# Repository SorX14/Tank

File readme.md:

## Tank ##

A project to learn about I2C comms and create a tank capable of travelling over tough terrain operating in manual PC, manual RC or full auto waypointing mode.

The design is centred around separate modules offloading the processing for each part to a separate processor. Most of this is wasteful as the chips are capable of much more, but I wanted to learn about I2C.

The tank has 2 standard RC ESCs with reverse, so require servo signalling which Ardiuno supports easily.

The controller board uses the much more powerful Teensy 3.1 which does all of the heavy lifting, and also powers a small OLED screen showing the current status.

It can be controlled with a normal RC transmitter, or using a radio linked to a PC. GPS coordinates can also be loaded into the tank to allow autonomous operation.

### PCB ###
Each PCB has its own readme in the seperate directories. All PCBs were ordered through [OSHPark](https://oshpark.com/) and they took 1 week to arrive once they're made by the fab house.

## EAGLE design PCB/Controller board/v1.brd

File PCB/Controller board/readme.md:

## Controller board ##

Connecting using the same RJ45 connector, this board has the 'brains' and radio modules for the tank.

The brains are provided by a [Teensy 3.1](https://www.pjrc.com/teensy/teensy31.html) which is a powerful, compact microprocessor by PJRC. The footprint was provided by forum user **Constantin**, available [here](http://forum.pjrc.com/threads/24637-Updated-Teensy-3-1-and-Teensy-3-0-Eagle-libraries). The Teensy 3.1. has multiple SPI, I2C and serial connections which is really useful for debugging and interfacing with other modules. Most importantly, the Teensy 3.1 has an Arduino compatible IDE addon - [TeensyDuino](https://www.pjrc.com/teensy/teensyduino.html) - which makes writing code for it much more familiar.

The radio is provided by an [ARF](http://shop.ciseco.co.uk/arf-high-power-radio-transceiver/) from Ciseco using their Eagle footprints. It could just as easily by an XRF, or XBEE as they are pin compatible.

There is also a footprint for an [SSD1306 OLED 128x64 display](http://forum.hobbycomponents.com/viewtopic.php?f=39&t=1517) which **bernebeer** made. 

The board also has a CR2032 battery holder footprint on the back which connects to the Teensy VBAT connection which keeps the built in RTC running.

There is a 'GPS' header with selectable voltage output - either 3.3v or 5v. This header is just a connection to a serial port on the Teensy so could be used for other modules.

The reset pad underneath the Teensy was designed to be soldered to one of the rectangular pads on the bottom of the Teensy with a short wire. The Teensy can reset itself via software, so its possible to tri-state this pin; reading the status or sending a reset pulse to other modules.

There are a couple of test points around the board for various voltages, or serial comms. There are 4 PWM pins available between the Teensy and the display.

There are RC controller headers, which will accept the signals generated by a standard RC receiver.

There are 2 'servo' outputs which will be used to control a RC car ESC.

### Parts list ###

- **Passives** - Not going to list them, all 0805 sized
- **RJ45 connector** - Molex 85504-5001 - Farnell no: 2313732
- **CR2032 holder** - Keystone 3 002 - RS Stock No: 219-7954
- **Watch crystal** - FOX ELECTRONICS NC26LF-327 - Farnell no: 2064057 (needed for the Teensy 3.1 to keep the time)

### Mistakes ###

The GPS header has the wrong silkscreen on it, so the GND and VCC are reversed. Most GPS units can handle reverse voltage, but double-check.

### Resources ###

- **PCB top** [https://github.com/SorX14/Tank/blob/master/PCB/Controller%20board/top.png](https://github.com/SorX14/Tank/blob/master/PCB/Controller%20board/top.png)
- **PCB bottom** [https://github.com/SorX14/Tank/blob/master/PCB/Controller%20board/bottom.png](https://github.com/SorX14/Tank/blob/master/PCB/Controller%20board/bottom.png)

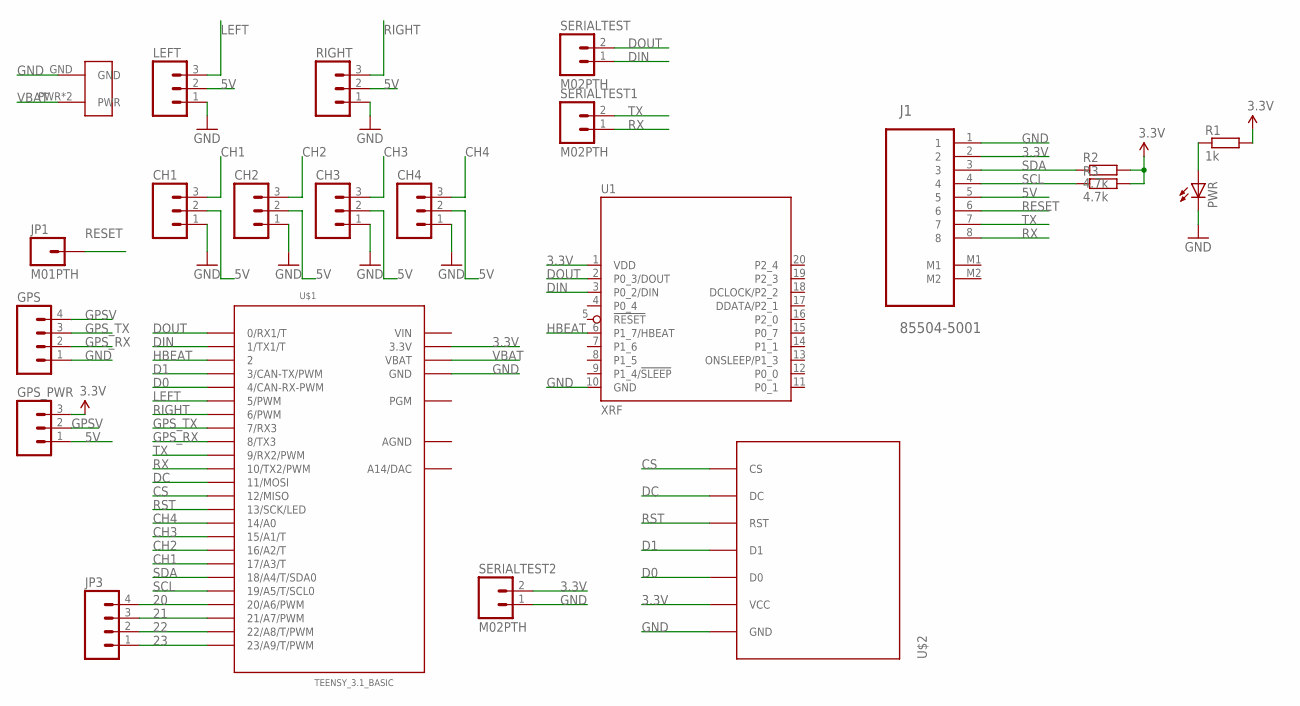
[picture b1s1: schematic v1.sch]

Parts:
CH1, CH2, CH3, CH4: M03PTH; 1X03
GPS: M04PTH; 1X04
GPS_PWR: M03PTH; 1X03
J1: 85504-5001; MOLEX_85504-5001
JP1: M01PTH; 1X01
JP3: M04PTH; 1X04
LEFT: M03PTH; 1X03
PWR: LEDCHIPLED_0805; CHIPLED_0805
R1: 1k; R0805
R2, R3: 4.7k; R0805
RIGHT: M03PTH; 1X03
SERIALTEST, SERIALTEST1, SERIALTEST2: M02PTH; 1X02
U1: XRF
U$1: TEENSY_3.1_BASIC
U$2: OLED_SSD1306_SPI
U$3: COINCELL

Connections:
3.3V: GPS_PWR.3, J1.2, R1.2, R2.2, R3.2, SERIALTEST2.2, U1.1 (VDD), U$1.3.3V, U$1.3.3V1 (3.3V), U$2.VCC
5V: CH1.2, CH2.2, CH3.2, CH4.2, GPS_PWR.1, J1.5, LEFT.2, RIGHT.2
20: JP3.4, U$1.20/A6 (20/A6/PWM)
21: JP3.3, U$1.21/A7 (21/A7/PWM)
22: JP3.2, U$1.22/A8 (22/A8/T/PWM)
23: JP3.1, U$1.23/A9 (23/A9/T/PWM)
AGND: U$1.AGND
CH1: CH1.3, U$1.17/A3 (17/A3/T)
CH2: CH2.3, U$1.16/A2 (16/A2/T)
CH3: CH3.3, U$1.15/A1 (15/A1/T)
CH4: CH4.3, U$1.14/A0
CS: U$1.12 (12/MISO), U$2.CS
D0: U$1.4 (4/CAN-RX-PWM), U$2.D0
D1: U$1.3 (3/CAN-TX/PWM), U$2.D1
DC: U$1.11 (11/MOSI), U$2.DC
DIN: SERIALTEST.1, U1.3 (P0_2/DIN), U$1.1 (1/TX1/T)
DOUT: SERIALTEST.2, U1.2 (P0_3/DOUT), U$1.0 (0/RX1/T)
GND: CH1.1, CH2.1, CH3.1, CH4.1, GPS.1, J1.1, LEFT.1, PWR.C, RIGHT.1, SERIALTEST2.1, U1.10 (GND), U$1.GND, U$1.GND1 (GND), U$2.GND, U$3.GND
GPSV: GPS.4, GPS_PWR.2
GPS_RX: GPS.2, U$1.8 (8/TX3)
GPS_TX: GPS.3, U$1.7 (7/RX3)
HBEAT: U1.6 (P1_7/HBEAT), U$1.2
LEFT: LEFT.3, U$1.5 (5/PWM)
unnamed: PWR.A, R1.1
RESET: J1.6, JP1.1
RIGHT: RIGHT.3, U$1.6 (6/PWM)
RST: U$1.13 (13/SCK/LED), U$2.RST
RX: J1.8, SERIALTEST1.1, U$1.10 (10/TX2/PWM)
SCL: J1.4, R3.1, U$1.19/A5 (19/A5/T/SCL0)
SDA: J1.3, R2.1, U$1.18/A4 (18/A4/T/SDA0)
TX: J1.7, SERIALTEST1.2, U$1.9 (9/RX2/PWM)
VBAT: U$1.VBAT, U$3.PWR, U$3.PWR2 (PWR)
VIN: U$1.VIN

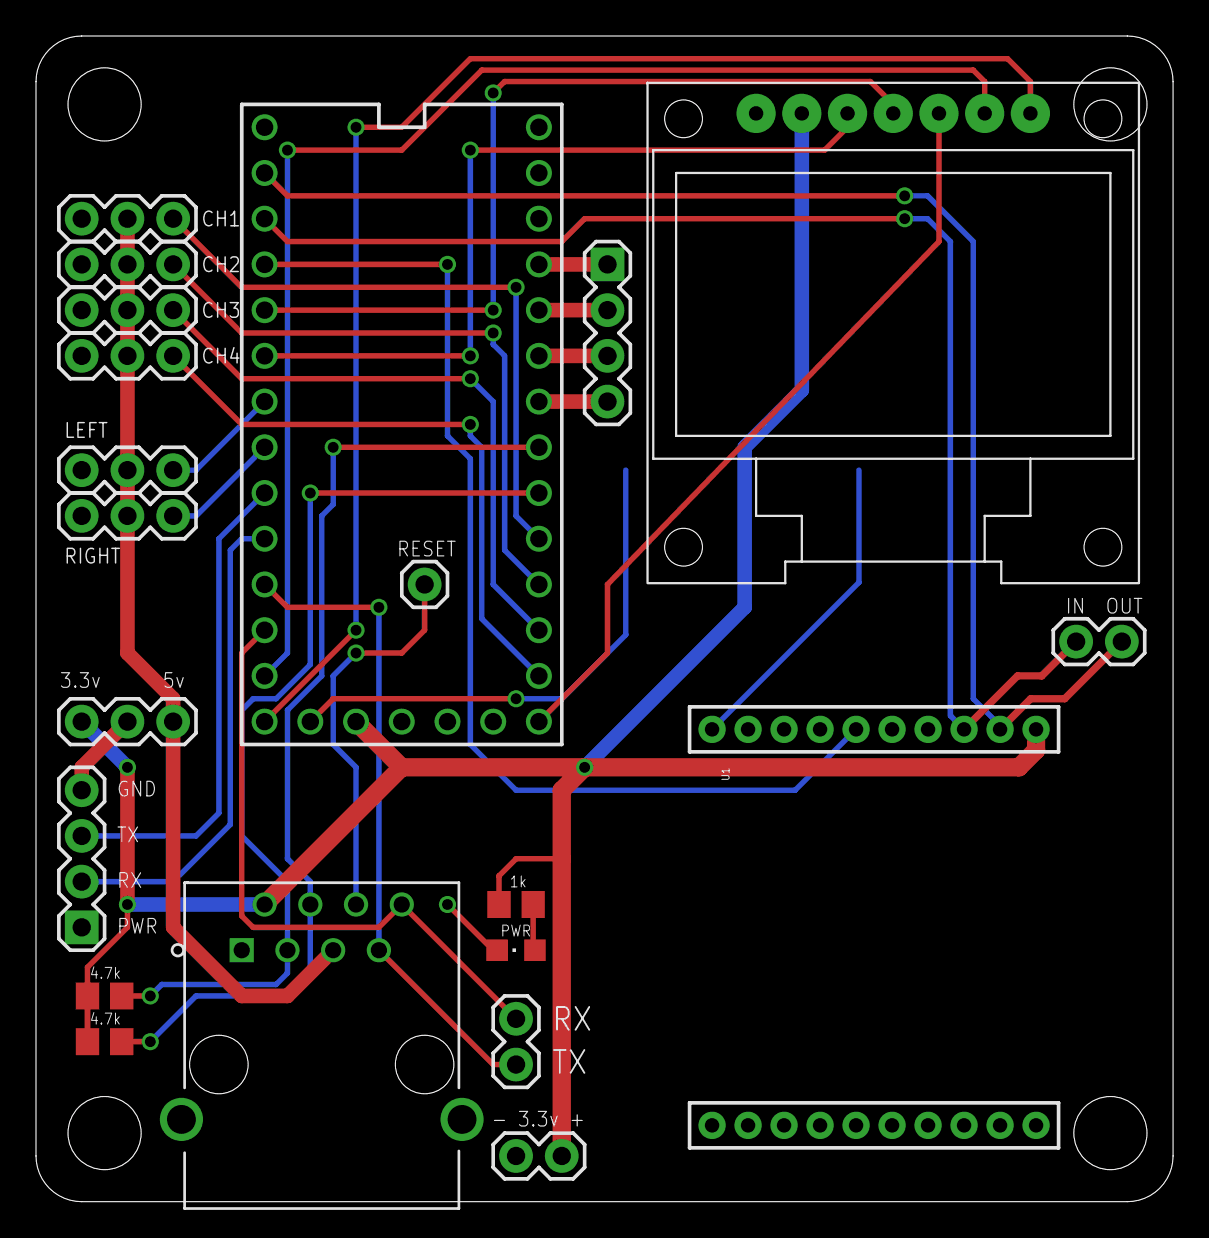
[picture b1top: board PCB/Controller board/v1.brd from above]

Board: 2 copper layers, 63.2 x 64.8 mm, 22 parts (1 on the bottom side), 31 nets.

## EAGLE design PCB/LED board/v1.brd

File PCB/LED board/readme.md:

## LED board ##

This board connects using the same RJ45 connector and pinout, and has the ability to drive 12V LED strips. 

There is no other sensors or pin breakouts on the board which is probably a mistake.

Runs @ 3.3v, and communicates via I2C or serial to a 'master' device. Has a footprint for a cap but in the end wasn't required, turns into a useful testing point for voltages.

The board is programmed via a custom shaped ISP header next to the RJ45 socket. There is a I2C active LED, along with a debug LED to help with testing.

The actual LED strip control side had a slice out of the ground plane to prevent ground loops. The MOSFETS can handle up to 20v, and a max dissipation of 1.3A.

There is a solder bridge up the top of the board that allows 2 boards to be programmed with the same code, and then one of them having the bridge closed; changing its I2C address.

### Parts list ###

- **Passives** - Not going to list them, all 0805 sized
- **RJ45 connector** - Molex 85504-5001 - Farnell no: 2313732
- **ATMEGA328P-AU** - TQFP-32 package - Farnell no: 1715486
- **SMD crystal** - 16 Mhz TXC 7B-16.000MAAJ-T - Farnell no: 1841977
- **N-channel MOSFETS** - NDS331N - Farnell no: 1839006
- **LEDs** - 0805 sized, various colours. Try and get the same brightness for each as otherwise it'll look strange.

### Mistakes ###

Rear silkscreen is mirrored.

### Resources ###

- **PCB top** [https://github.com/SorX14/Tank/blob/master/PCB/LED%20board/top.png](https://github.com/SorX14/Tank/blob/master/PCB/LED%20board/top.png)
- **PCB bottom** [https://github.com/SorX14/Tank/blob/master/PCB/LED%20board/bottom.png](https://github.com/SorX14/Tank/blob/master/PCB/LED%20board/bottom.png)

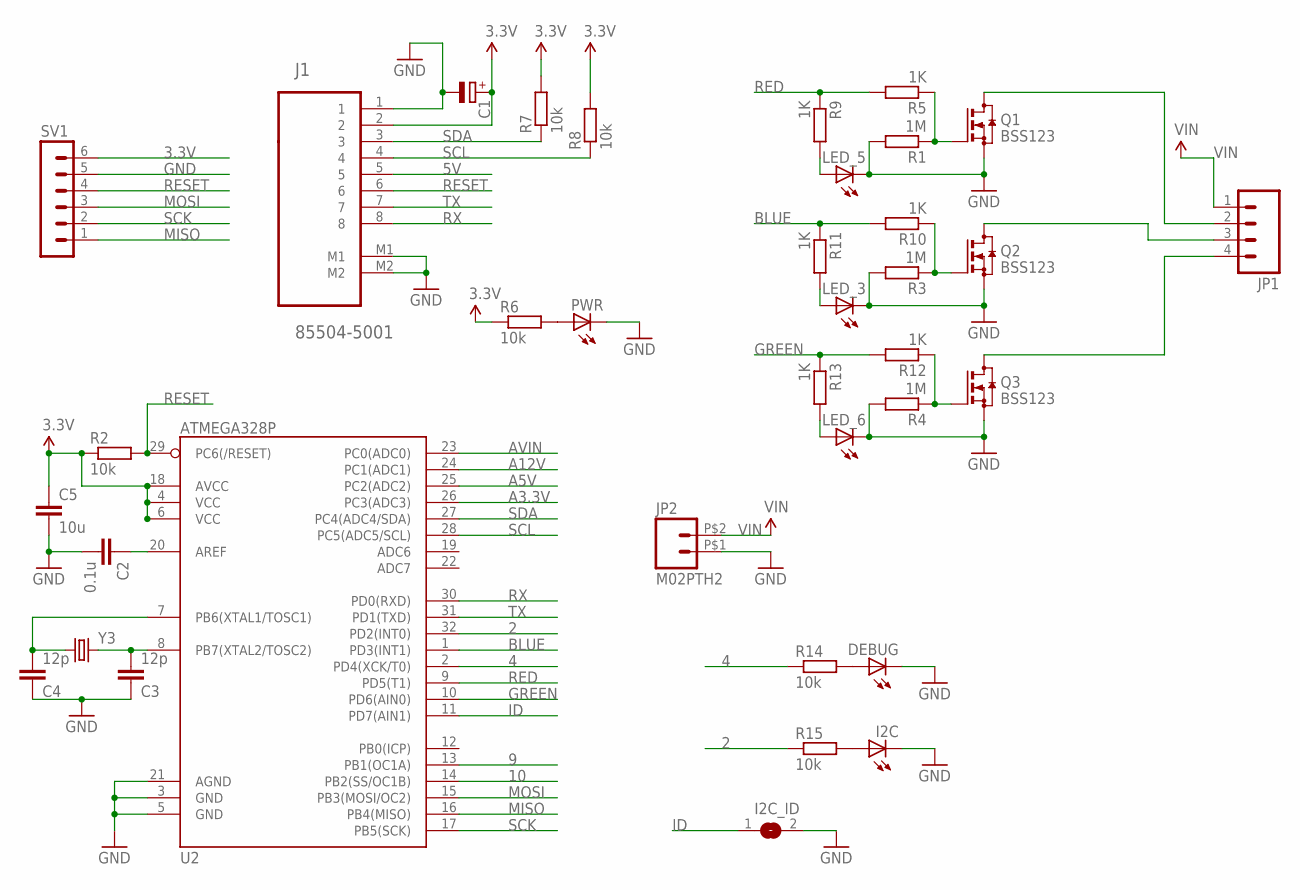
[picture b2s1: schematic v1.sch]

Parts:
C1: CPOL-EUE2.5-6; E2,5-6
C2: 0.1u; C0805
C3, C4: 12p; C0805
C5: 10u; C0805
DEBUG: LEDSML0805; SML0805
I2C: LEDSML0805; SML0805
I2C_ID: SJ
J1: 85504-5001; MOLEX_85504-5001
JP1: M04POLAR; MOLEX-1X4
JP2: M02PTH2; 1X02_BIG
LED_3, LED_5, LED_6: LEDSML0805; SML0805
PWR: LEDSML0805; SML0805
Q1, Q2, Q3: BSS123; SOT23
R1, R3, R4: 1M; R0805
R2, R6, R7, R8, R14, R15: 10k; R0805
R5, R9, R10, R11, R12, R13: 1K; R0805
SV1: MA06-1
U2: ATMEGA328P; TQFP32-08
Y3: CRYSTALCRYSTAL-SMD-5X3-LARGEPAD; CRYSTAL-SMD-5X3

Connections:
2: R15.1, U2.32 (PD2(INT0))
3.3V: C1.+, C5.1, J1.2, R2.1, R6.1, R7.2, R8.2, SV1.6, U2.4 (VCC), U2.6 (VCC), U2.18 (AVCC)
4: R14.1, U2.2 (PD4(XCK/T0))
5V: J1.5
9: U2.13 (PB1(OC1A))
10: U2.14 (PB2(SS/OC1B))
A3.3V: U2.26 (PC3(ADC3))
A5V: U2.25 (PC2(ADC2))
A12V: U2.24 (PC1(ADC1))
AVIN: U2.23 (PC0(ADC0))
BLUE: R10.2, R11.1, U2.1 (PD3(INT1))
GND: C1.-, C2.2, C3.1, C4.1, C5.2, DEBUG.C, I2C.C, I2C_ID.2, J1.1, J1.M1, J1.M2, JP2.P$1 (1), LED_3.C, LED_5.C, LED_6.C, PWR.C, Q1.2 (S), Q2.2 (S), Q3.2 (S), R1.2, R3.2, R4.2, SV1.5, U2.3 (GND), U2.5 (GND), U2.21 (AGND)
GREEN: R12.2, R13.1, U2.10 (PD6(AIN0))
ID: I2C_ID.1, U2.11 (PD7(AIN1))
MISO: SV1.1, U2.16 (PB4(MISO))
MOSI: SV1.3, U2.15 (PB3(MOSI/OC2))
unnamed: JP1.2, Q1.3 (D)
unnamed: C2.1, U2.20 (AREF)
unnamed: C3.2, U2.8 (PB7(XTAL2/TOSC2)), Y3.3 (2)
unnamed: C4.2, U2.7 (PB6(XTAL1/TOSC1)), Y3.1
unnamed: JP1.3, Q2.3 (D)
unnamed: JP1.4, Q3.3 (D)
unnamed: Q1.1 (G), R1.1, R5.1
unnamed: Q2.1 (G), R3.1, R10.1
unnamed: Q3.1 (G), R4.1, R12.1
unnamed: DEBUG.A, R14.2
unnamed: PWR.A, R6.2
unnamed: I2C.A, R15.2
unnamed: LED_5.A, R9.2
unnamed: LED_3.A, R11.2
unnamed: LED_6.A, R13.2
RED: R5.2, R9.1, U2.9 (PD5(T1))
RESET: J1.6, R2.2, SV1.4, U2.29 (PC6(/RESET))
RX: J1.8, U2.30 (PD0(RXD))
SCK: SV1.2, U2.17 (PB5(SCK))
SCL: J1.4, R8.1, U2.28 (PC5(ADC5/SCL))
SDA: J1.3, R7.1, U2.27 (PC4(ADC4/SDA))
TX: J1.7, U2.31 (PD1(TXD))
VIN: JP1.1, JP2.P$2 (2)

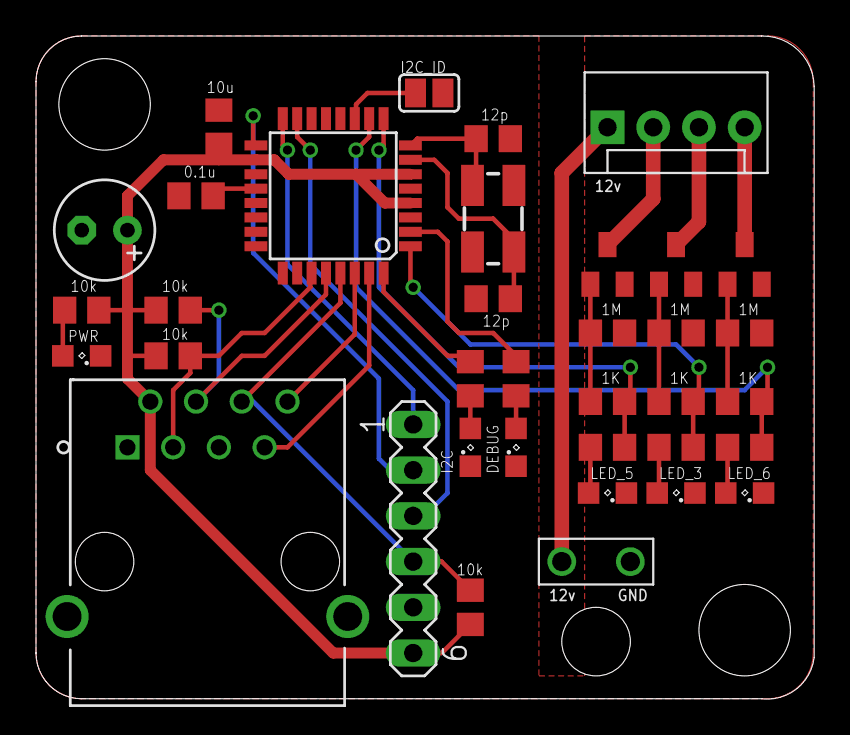
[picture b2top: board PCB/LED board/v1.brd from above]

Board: 2 copper layers, 43.2 x 36.8 mm, 36 parts (0 on the bottom side), 32 nets.

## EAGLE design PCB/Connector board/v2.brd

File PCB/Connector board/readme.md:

## Connector board ##

Simple connector board that has 6 RJ45 sockets and allows you to connect 6 boards together, with 2 of them having the ability to connect the serial channels together (ports 4 and 5 to port 1).

There is a reset button on the board which will reset all of the boards that are connected if they implement the reset pin connection.

The design vaguely implies that the voltage board connects to port 4 and the controller board port 1. Any other modules can connect to the other ports. Another connector board could be used to daisy-chain for more connections.

### Parts list ###

- **RJ45 connector** - Molex 85504-5001 - Farnell no: 2313732
- **0805 10k resistor** - Should be easy enough to find
- **Tactile button** - Salvaged one from another project, again easy to find

### Resources ###

- **PCB top** [https://github.com/SorX14/Tank/blob/master/PCB/Connector%20board/top.png](https://github.com/SorX14/Tank/blob/master/PCB/Connector%20board/top.png)
- **PCB bottom** [https://github.com/SorX14/Tank/blob/master/PCB/Connector%20board/bottom.png](https://github.com/SorX14/Tank/blob/master/PCB/Connector%20board/bottom.png)

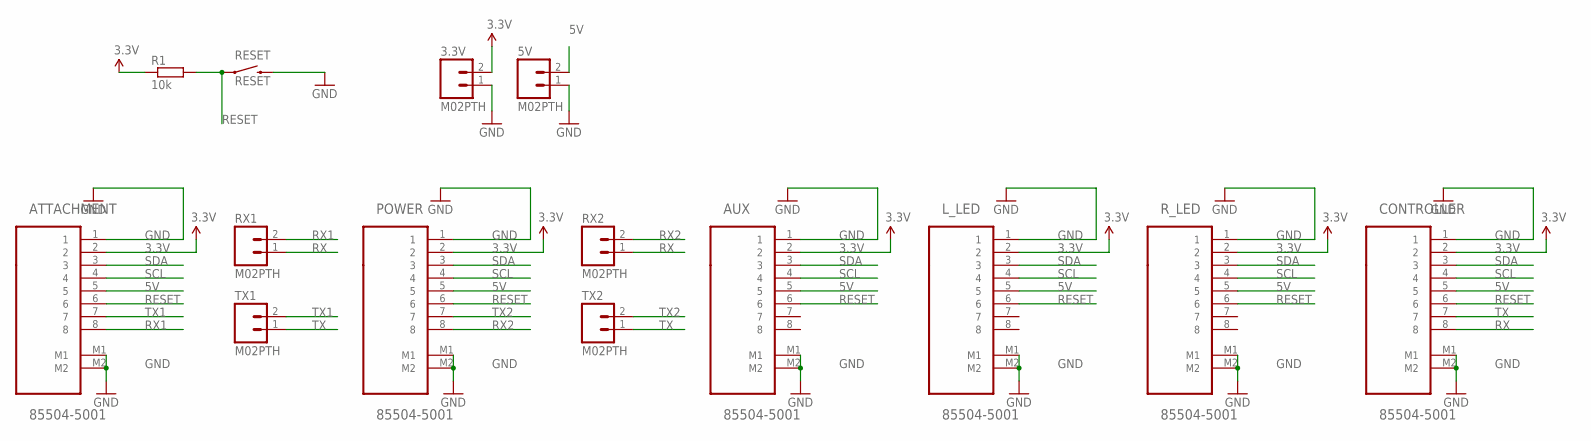
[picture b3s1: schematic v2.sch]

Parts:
3.3V, 5V: M02PTH; 1X02
ATTACHMENT: 85504-5001; MOLEX_85504-5001
AUX: 85504-5001; MOLEX_85504-5001
CONTROLLER: 85504-5001; MOLEX_85504-5001
L_LED: 85504-5001; MOLEX_85504-5001
POWER: 85504-5001; MOLEX_85504-5001
R1: 10k; R0805
RESET: RESET; TACTILE-PTH
RX1, RX2: M02PTH; 1X02
R_LED: 85504-5001; MOLEX_85504-5001
TX1, TX2: M02PTH; 1X02

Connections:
3.3V: 3.3V.2, ATTACHMENT.2, AUX.2, CONTROLLER.2, L_LED.2, POWER.2, R1.1, R_LED.2
5V: 5V.2, ATTACHMENT.5, AUX.5, CONTROLLER.5, L_LED.5, POWER.5, R_LED.5
GND: 3.3V.1, 5V.1, ATTACHMENT.1, ATTACHMENT.M1, ATTACHMENT.M2, AUX.1, AUX.M1, AUX.M2, CONTROLLER.1, CONTROLLER.M1, CONTROLLER.M2, L_LED.1, L_LED.M1, L_LED.M2, POWER.1, POWER.M1, POWER.M2, RESET.3 (2), R_LED.1, R_LED.M1, R_LED.M2
RESET: ATTACHMENT.6, AUX.6, CONTROLLER.6, L_LED.6, POWER.6, R1.2, RESET.1, R_LED.6
RX: CONTROLLER.8, RX1.1, RX2.1
RX1: ATTACHMENT.8, RX1.2
RX2: POWER.8, RX2.2
SCL: ATTACHMENT.4, AUX.4, CONTROLLER.4, L_LED.4, POWER.4, R_LED.4
SDA: ATTACHMENT.3, AUX.3, CONTROLLER.3, L_LED.3, POWER.3, R_LED.3
TX: CONTROLLER.7, TX1.1, TX2.1
TX1: ATTACHMENT.7, TX1.2
TX2: POWER.7, TX2.2

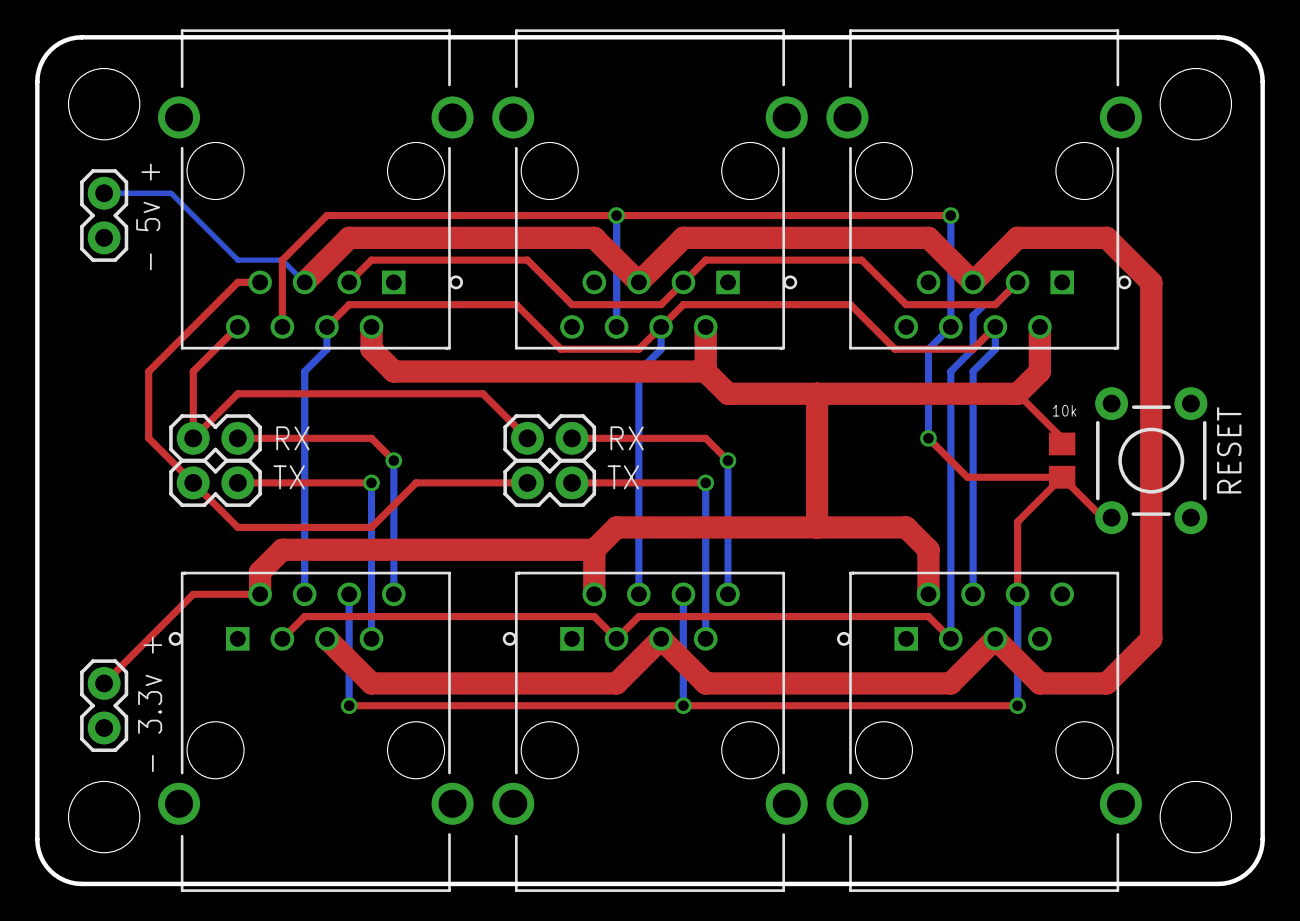
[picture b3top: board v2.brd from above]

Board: 2 copper layers, 69.8 x 48.3 mm, 14 parts (0 on the bottom side), 12 nets.

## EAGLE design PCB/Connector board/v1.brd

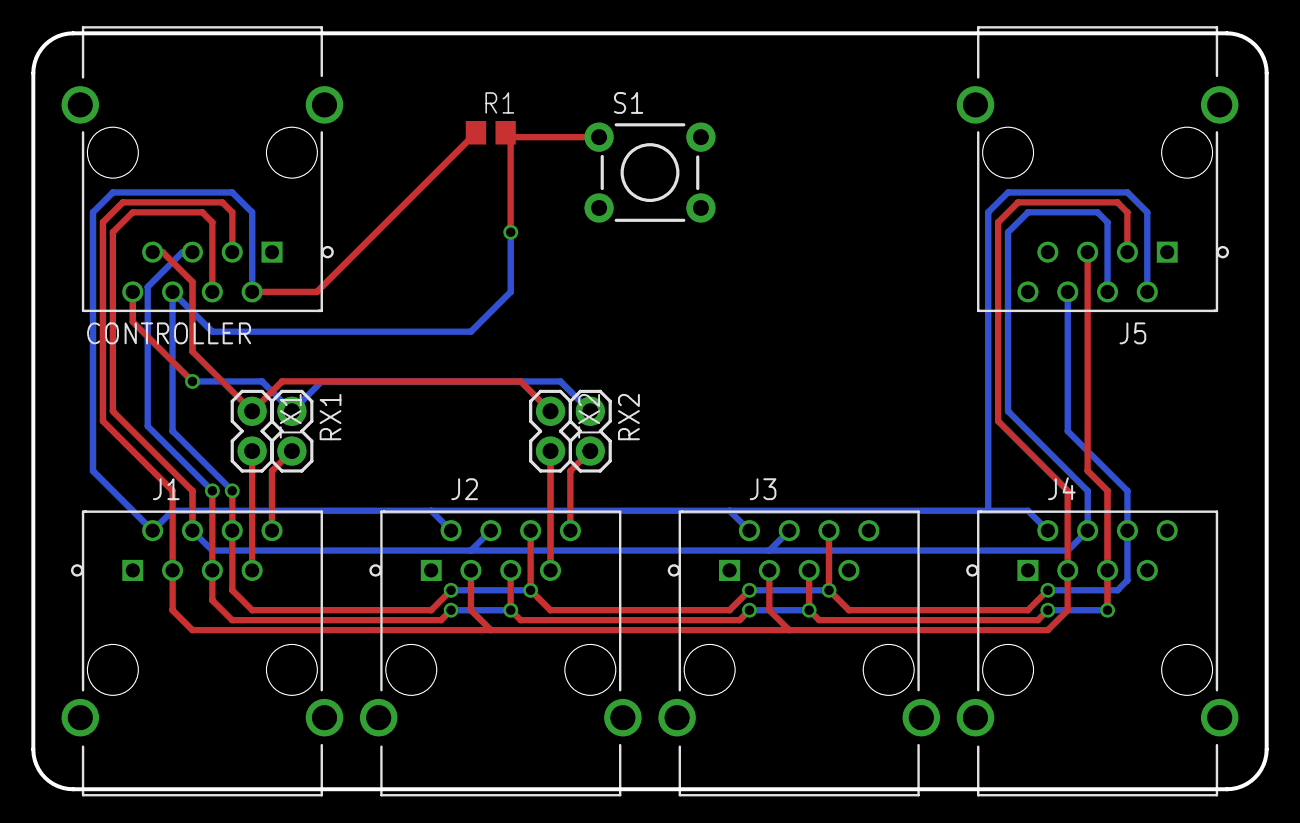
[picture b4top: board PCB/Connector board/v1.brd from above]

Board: 2 copper layers, 78.7 x 48.3 mm, 12 parts (0 on the bottom side), 12 nets.

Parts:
CONTROLLER: 85504-5001; MOLEX_85504-5001
J1, J2, J3, J4, J5: 85504-5001; MOLEX_85504-5001
R1: R0805
RX1, RX2: M02PTH; 1X02
S1: SWITCH-MOMENTARY-2PTH; TACTILE-PTH
TX1, TX2: M02PTH; 1X02

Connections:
3.3V: CONTROLLER.2, J1.2, J2.2, J3.2, J4.2, J5.2, R1.1
5V: CONTROLLER.5, J1.5, J2.5, J3.5, J4.5, J5.5
GND: CONTROLLER.1, CONTROLLER.M1, CONTROLLER.M2, J1.1, J1.M1, J1.M2, J2.1, J2.M1, J2.M2, J3.1, J3.M1, J3.M2, J4.1, J4.M1, J4.M2, J5.1, J5.M1, J5.M2, S1.3
RESET: CONTROLLER.6, J1.6, J2.6, J3.6, J4.6, J5.6, R1.2, S1.1
RX: CONTROLLER.8, RX1.1, RX2.1
RX1: J1.8, RX1.2
RX2: J2.8, RX2.2
SCL: CONTROLLER.4, J1.4, J2.4, J3.4, J4.4, J5.4
SDA: CONTROLLER.3, J1.3, J2.3, J3.3, J4.3, J5.3
TX: CONTROLLER.7, TX1.1, TX2.1
TX1: J1.7, TX1.2
TX2: J2.7, TX2.2

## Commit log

2014-07-21 :circus_tent: Added .gitattributes & .gitignore files
2014-07-21 Readme for LED board
2014-07-21 Updating documentation
2014-07-21 Updated readme documentation
2014-07-21 Adding controller source files
2014-07-21 Adding main readme
2014-07-21 Adding PCB
2014-07-21 Sync
2014-07-21 Adding tilt compensation
2014-07-21 Adding voltage low-pass filtering
2014-07-22 I2C improvements
    Updated hasComms method to include the IMU
    Improved the layout and structure of the IMU acquisition code
    Improved commenting
2014-07-22 Adding GPS capability
2014-07-22 Adding GPS functions
2014-07-22 Variables and adding GPS functions
2014-07-29 Fixed IMU issues (signed not unsigned int)
2014-08-04 PCB images and RC control
    Added OSH Park renders of the PCBs, updated the code to allow control
    via RC
2014-08-04 Updated documentation with PCB images
2014-08-04 Adding XRF communication via library
    Untested and no idea if it compiles. Needs a separate library to run
2014-08-06 Adding XRF library and framerate
2014-08-12 Add schematic images

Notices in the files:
parts and their libraries:
SparkFun-Connectors: Licensing: CC v3.0 Share-Alike You are welcome to use this library for commercial purposes.
